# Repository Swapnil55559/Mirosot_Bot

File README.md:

# Mirosot

This repository houses the comprehensive design and documentation for an autonomously controlled bot, encompassing the following key components:

#### Board Design and Schematic:

 - Employs an ESP32 microcontroller as the foundation of the main circuit board.
 - Faulhaber Series 2224SR encoded brushed DC motors are used (Having 6 pinout: +M, -M, +5V, GND, Encoder A and Encoder B)
 - DRV8833 Motor driver and buck converter is used (Requires 3S Lipo battery).
 - 5V logic level shifting to 3.3 logic level for Encoder using diodes in reverse bias
 - DRV8833 is always enabled by shorting the JP jumper at the back of the breakout board
 - Extra GPIO LED are added, one of which is for low battery voltage warning (Battery voltage is read by ESP32)

#### Embedded Code:

 - Implements wireless communication using the UDP protocol.
 - Based on position the bot as a UDP client receives velocity commands for both wheels.
 - Leverages a precise velocity control algorithm (PID controller) to achieve the specified RPM and direction.
 - The velocity is read by counting the number of pulses in 1ms (each pulse triggers an interrupt on rising edge and increments the counter of pulse)
 - There are three header files included, "driver.h", "encoder.h", and "motorcontrol.h". The latter depends on the former two.

## Connections

* Motor +M and -M pins are connected to GPIO 25 and 26 or 33 and 32 of ESP32
* Motor Encoder A and Encoder B pins are connected to GPIO 18 and 19 or 36 and 39
* Battery refernce voltage is connected Analog Input pin 35 (12 bit resolution)
* GPIO LED are connected to GPIO pins 13, 14 and 27. The battery low voltage warning LED is connected to GPIO 12

## Instructions

In order to use this header for motor control, first make sure you have the proper connections, as explained above. Then, just `#include "motorcontrol.h"` and initialise a **motorcontrol** object as
`motorcontrol objectname(M+, M-, Channel 1, channel 2, Encoder pin 1, Encoder pin 2)`

`Channel 1` is the PWM channel that is going to be used\
`Channel 2` another PWM channel to drive the motor according to the calculated duty cycle

This object has the following public member functions:

* `void init()` initialises the **motorcontrol** object

* `void refresh()` sets the current velocity and previous velocity as 0

* `void update_state()` updates the previous velocity and previous time counter, assigns current velocity and current time counter

* `float get_velocity()` return the current velocity 
* `void setvel_setpoint(float vel, char dir)` excecutes a single loop of velocity control, calculates proportional, dervative and integral error, then computes the duty cycle and drives the motor with calculated duty cycle.
* `kp`, `kd` and `ki` are public class members, thus we can have tune both the motors independantly. object of class `driver` and `encoder` is also public member of `motorcontrol` class because we need to call `cal_vel_callback()` method of class `encoder` in ISR
Inside the `ino` file we need to initialise UDP class by using header files `#include  <WiFiUdp.h>` and `#include <WiFi.h>` then define the `WIFI_SSID`, `WIFI_PASSWORD` and `UDP_PORT`

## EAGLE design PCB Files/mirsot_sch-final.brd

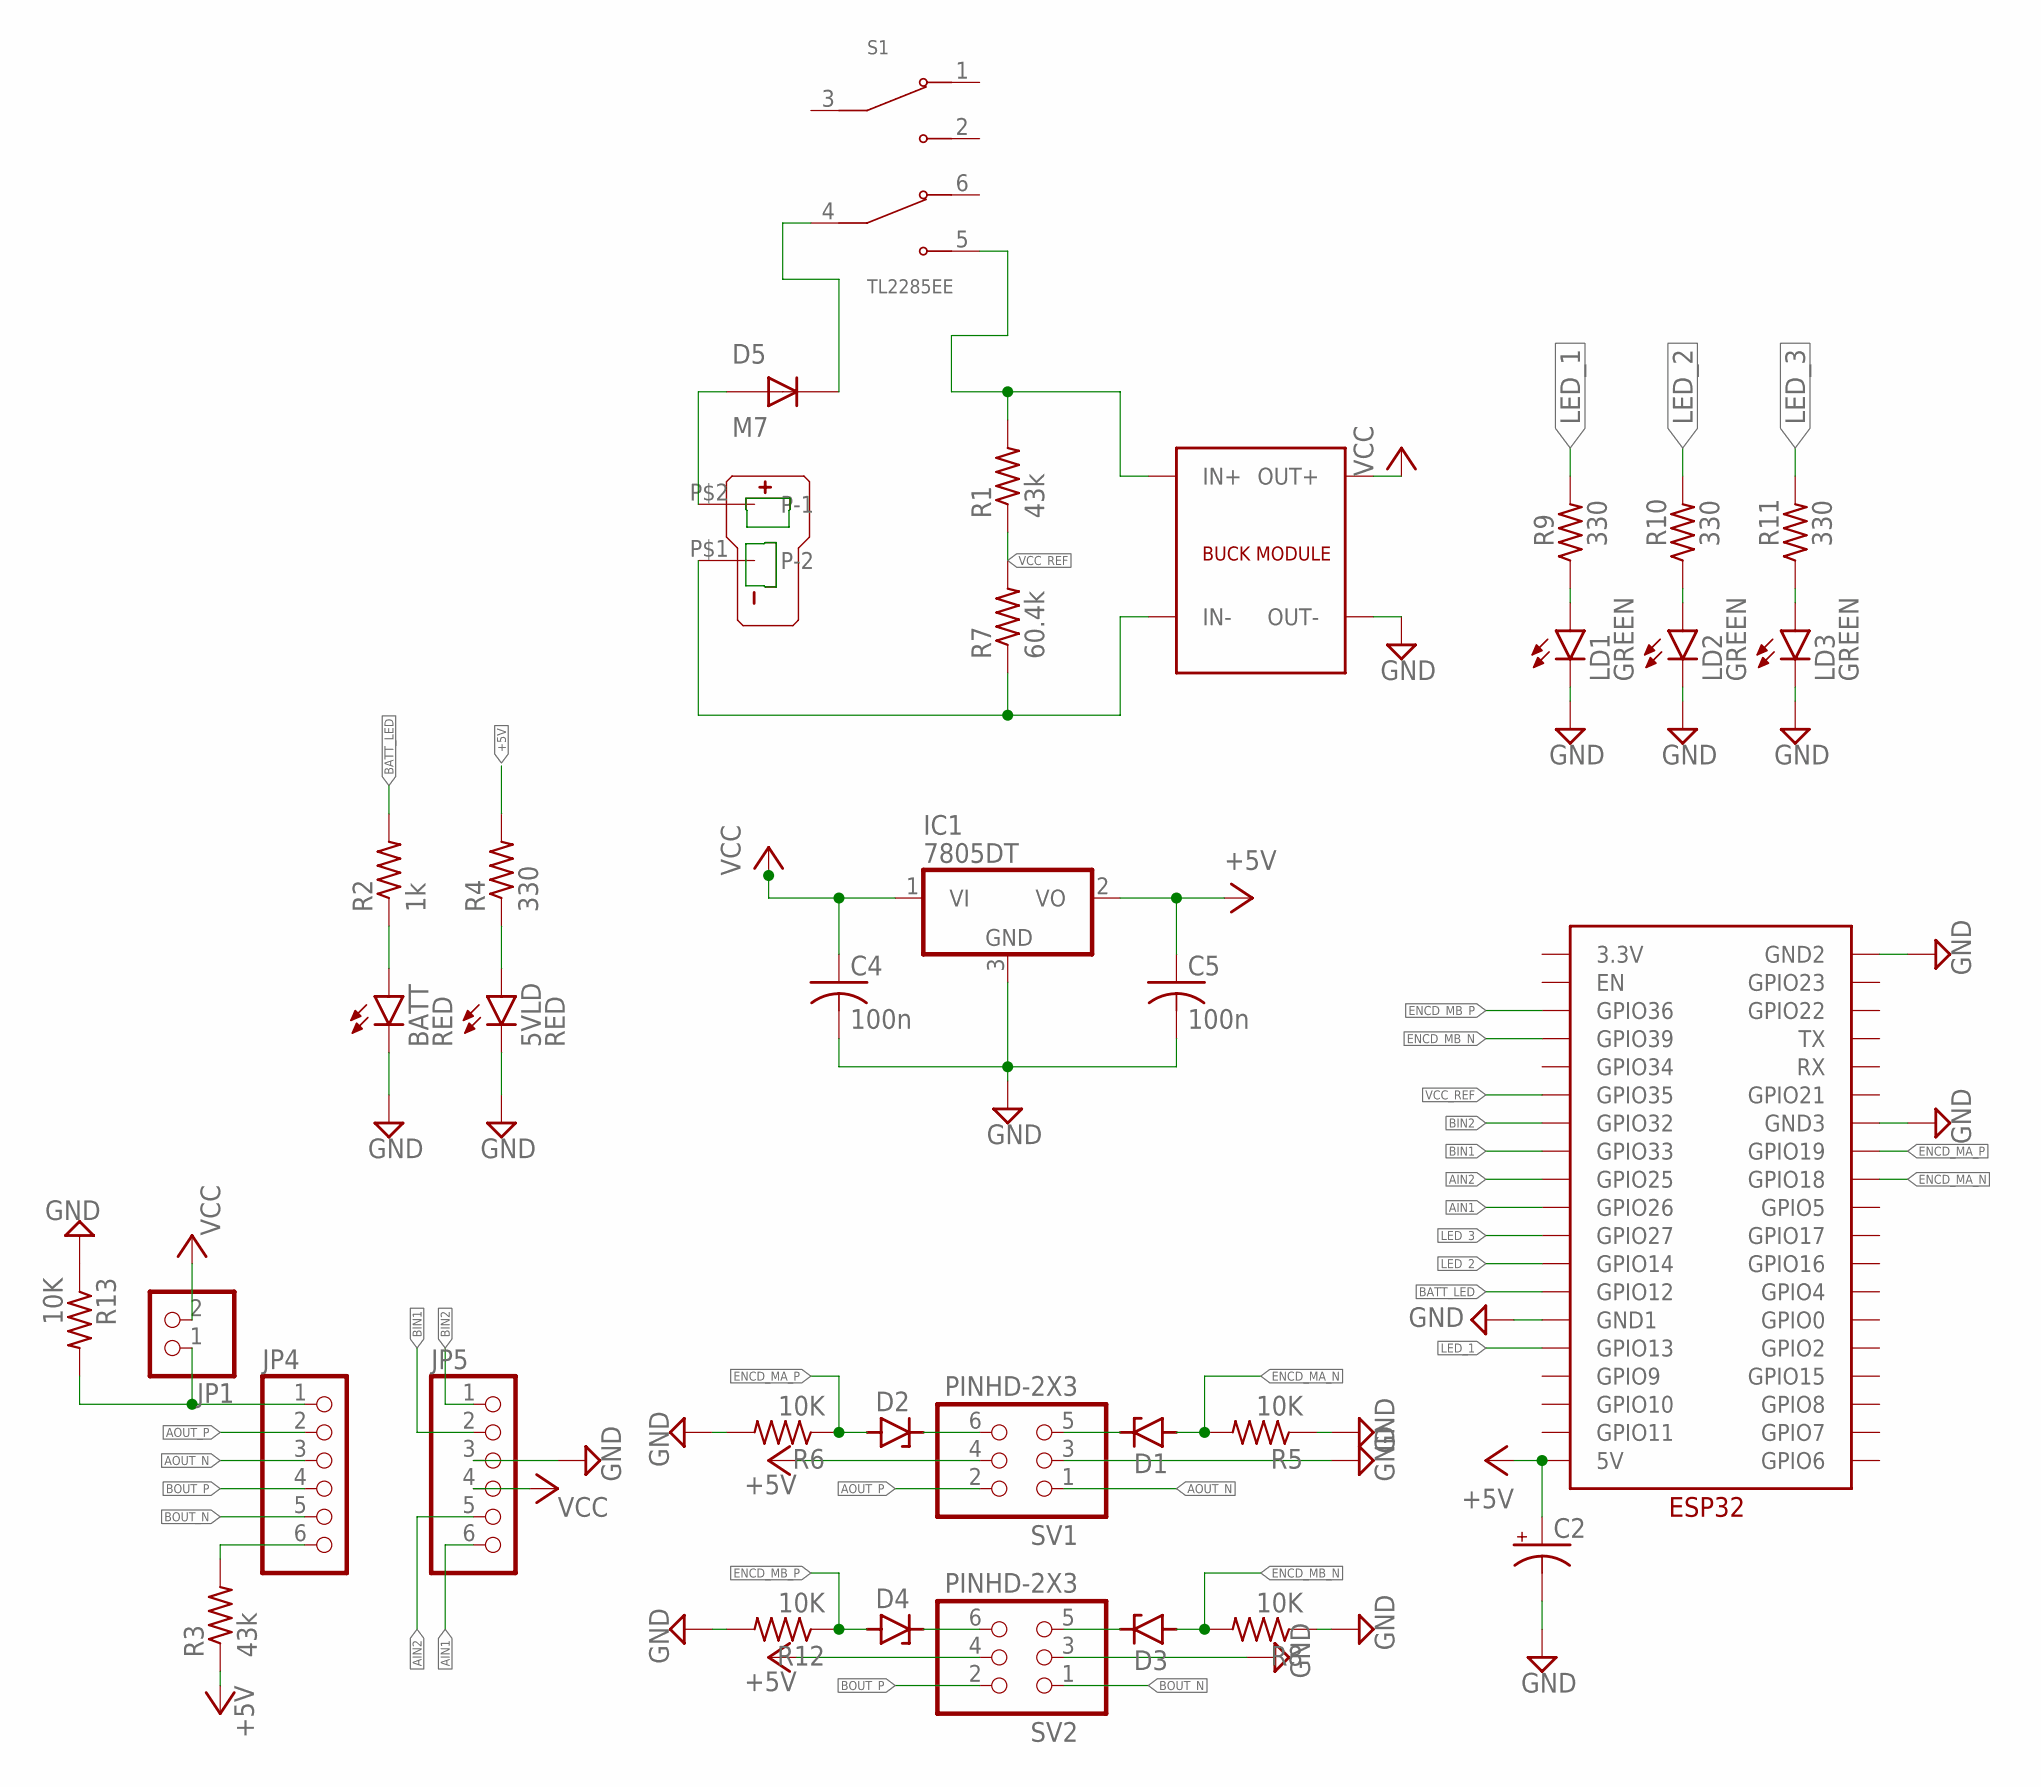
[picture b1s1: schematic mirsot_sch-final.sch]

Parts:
5VLD: RED; SML1206
BATT: RED; SML1206
C2: CPOL-USE2.5-6; E2,5-6
C4, C5: 100n; C0603K
D1, D2, D3, D4: ZENER-DIODEDO34-7; DO34Z7
D5: M7; DIOM505270X240
IC1: 7805DT; TO252
JP1: PINHD-1X2; 1X02
JP4, JP5: PINHD-1X6; 1X06
LD1, LD2, LD3: GREEN; SML1206
R1, R3: 43k; M1206
R2: 1k; M1206
R4, R9, R10, R11: 330; M1206
R5, R6, R8, R12, R13: 10K; M1206
R7: 60.4k; M1206
S1: TL2285EE; SW_TL2285EE
SV1, SV2: PINHD-2X3; 2X03
U$1: T_PLUG_CONNECTOR_H
U$2: ESP32
U$3: BUCK_CONVERTER

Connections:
+5V: C2.+, C5.1, IC1.2 (VO), R3.1, R4.2, SV1.4, SV2.4, U$2.5V
AIN1: JP5.6, U$2.GPIO26
AIN2: JP5.5, U$2.GPIO25
AOUT_N: JP4.3, SV1.1
AOUT_P: JP4.2, SV1.2
BATT_LED: R2.2, U$2.GPIO12
BIN1: JP5.2, U$2.GPIO33
BIN2: JP5.1, U$2.GPIO32
BOUT_N: JP4.5, SV2.1
BOUT_P: JP4.4, SV2.2
ENCD_MA_N: D1.A, R5.2, U$2.GPIO18
ENCD_MA_P: D2.A, R6.1, U$2.GPIO19
ENCD_MB_N: D3.A, R8.2, U$2.GPIO39
ENCD_MB_P: D4.A, R12.1, U$2.GPIO36
GND: 5VLD.C, BATT.C, C2.-, C4.2, C5.2, IC1.3 (GND), JP5.3, LD1.C, LD2.C, LD3.C, R5.1, R6.2, R8.1, R12.2, R13.1, SV1.3, SV2.3, U$2.GND1, U$2.GND2, U$2.GND3, U$3.OUT-
LED_1: R9.2, U$2.GPIO13
LED_2: R10.2, U$2.GPIO14
LED_3: R11.2, U$2.GPIO27
unnamed: JP4.6, R3.2
unnamed: BATT.A, R2.1
unnamed: LD1.A, R9.1
unnamed: LD2.A, R10.1
unnamed: 5VLD.A, R4.1
unnamed: D1.C, SV1.5
unnamed: D2.C, SV1.6
unnamed: D3.C, SV2.5
unnamed: LD3.A, R11.1
unnamed: D4.C, SV2.6
unnamed: D5.A, U$1.P$2 (P-1)
unnamed: JP1.1, JP4.1, R13.2
unnamed: D5.C, S1.4 (COM2)
unnamed: R1.2, S1.5 (NO2), U$3.IN+
unnamed: R7.1, U$1.P$1 (P-2), U$3.IN-
VCC: C4.1, IC1.1 (VI), JP1.2, JP5.4, U$3.OUT+
VCC_REF: R1.1, R7.2, U$2.GPIO35

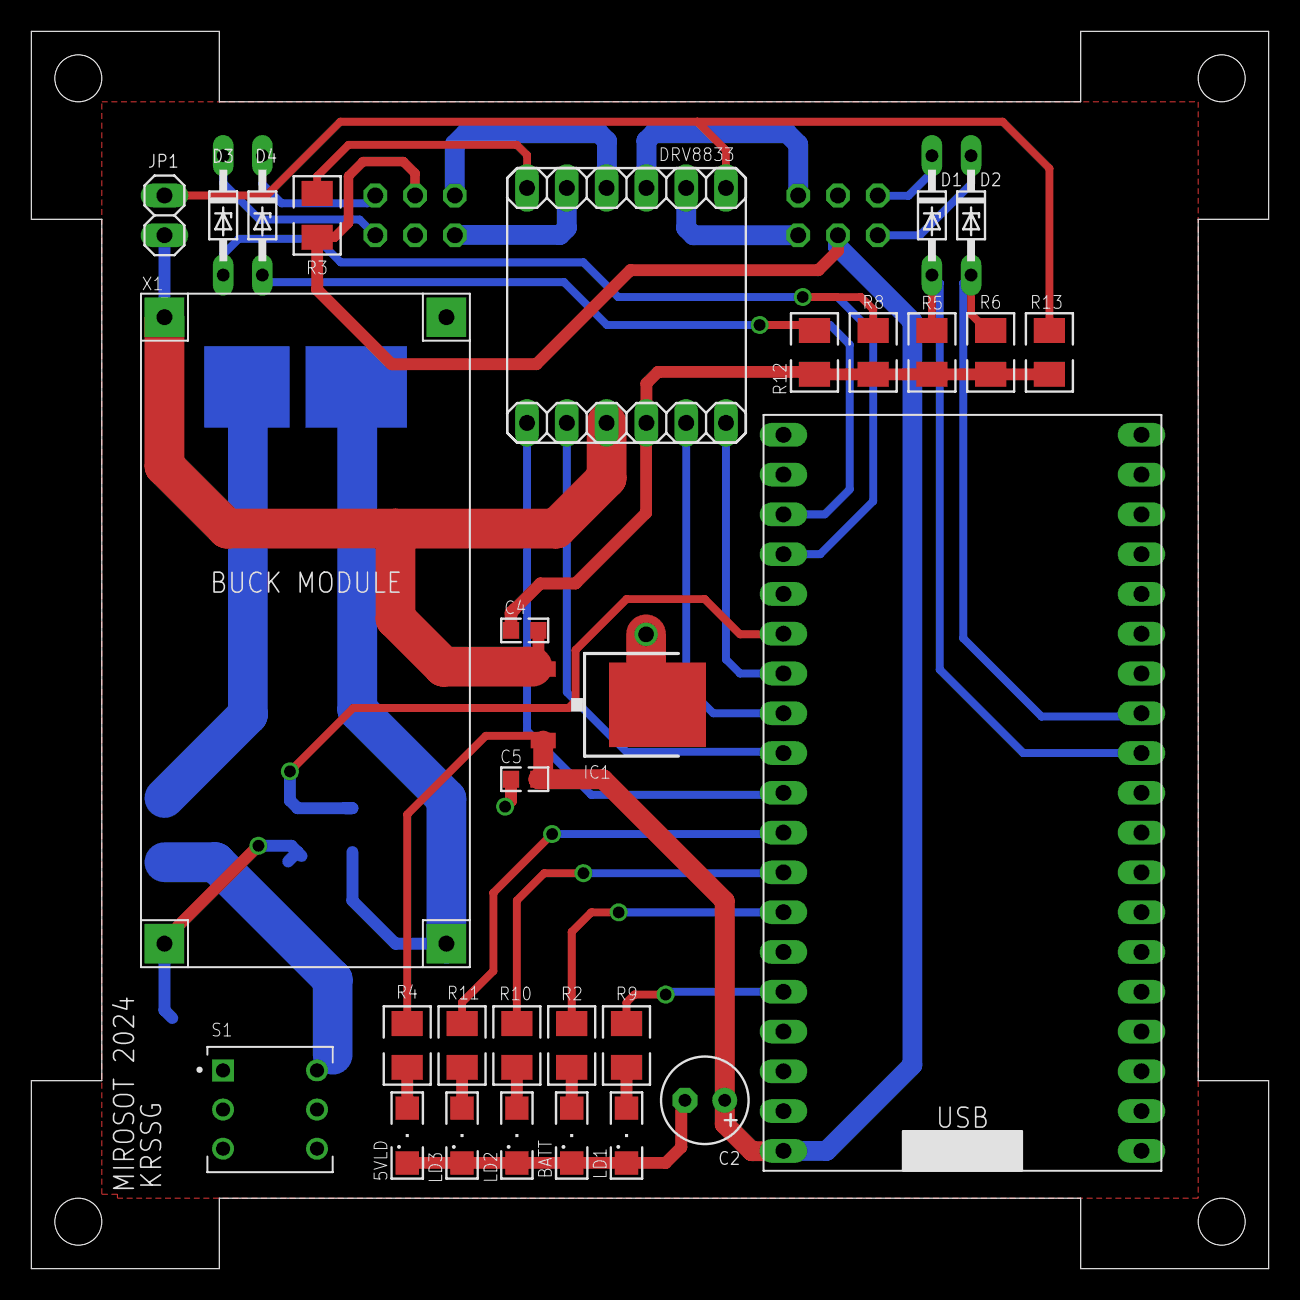
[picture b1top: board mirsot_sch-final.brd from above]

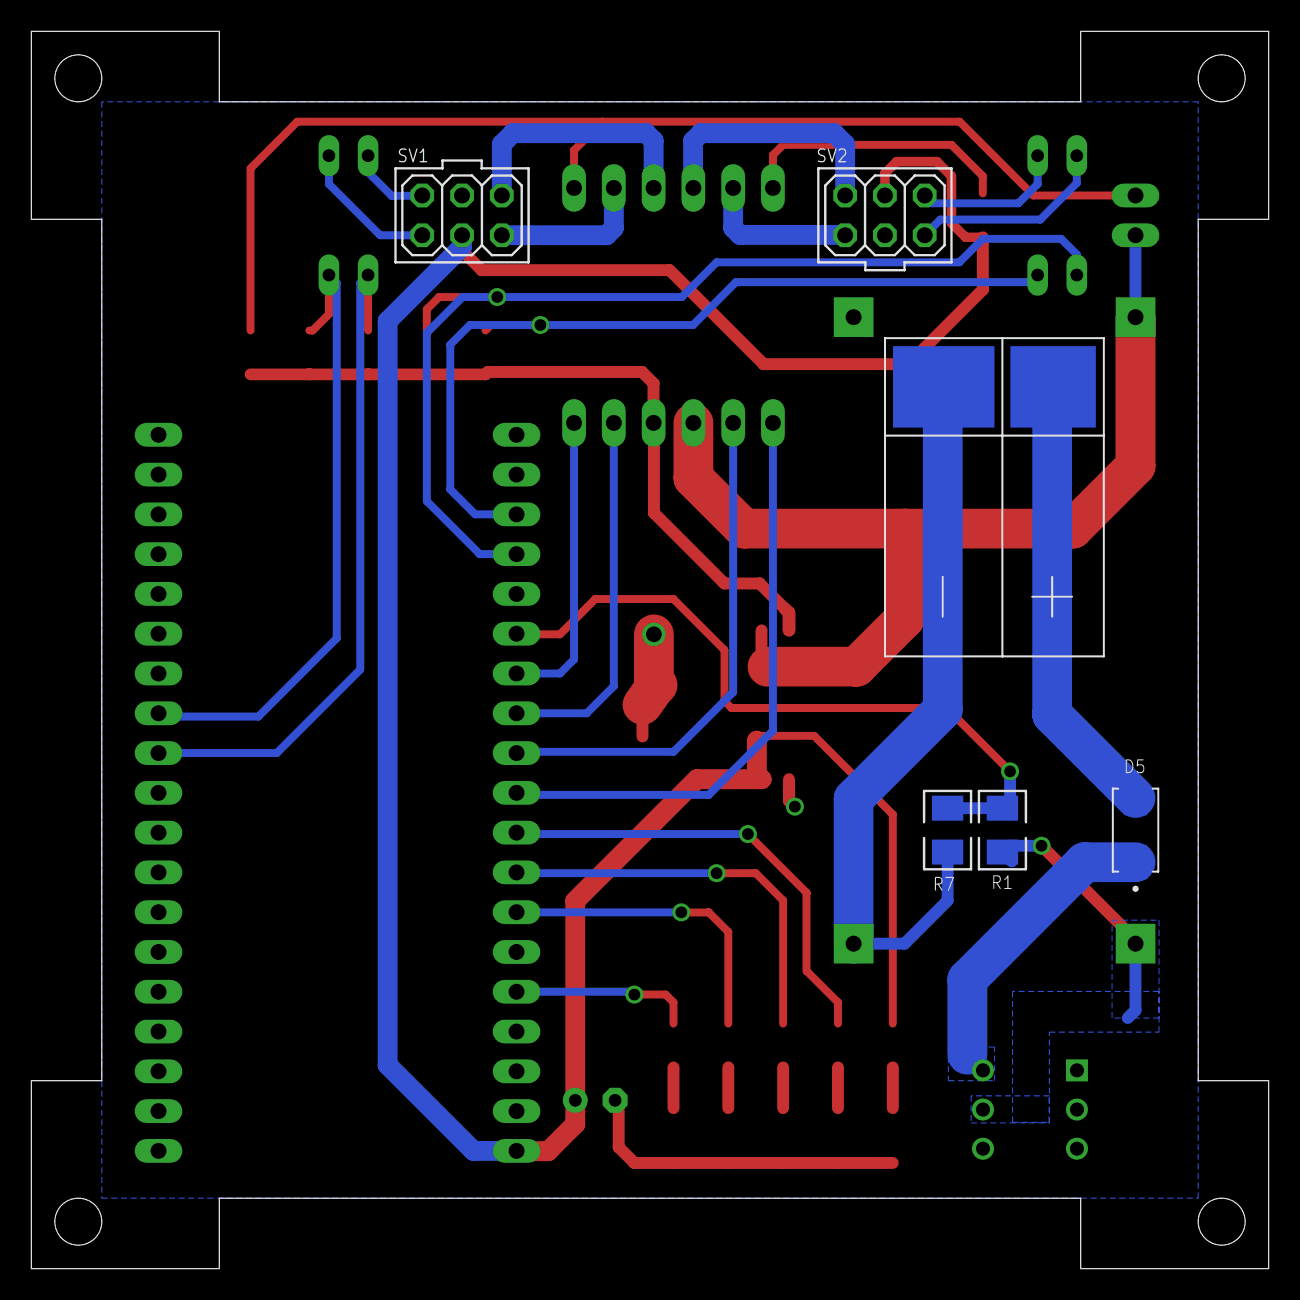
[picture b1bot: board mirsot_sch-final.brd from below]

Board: 2 copper layers, 79.0 x 79.0 mm, 36 parts (6 on the bottom side), 35 nets.

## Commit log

2024-01-06 First commit
    V1
